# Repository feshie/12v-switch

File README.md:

12v-switch
==========

A simple FET switch with powerpole in/out

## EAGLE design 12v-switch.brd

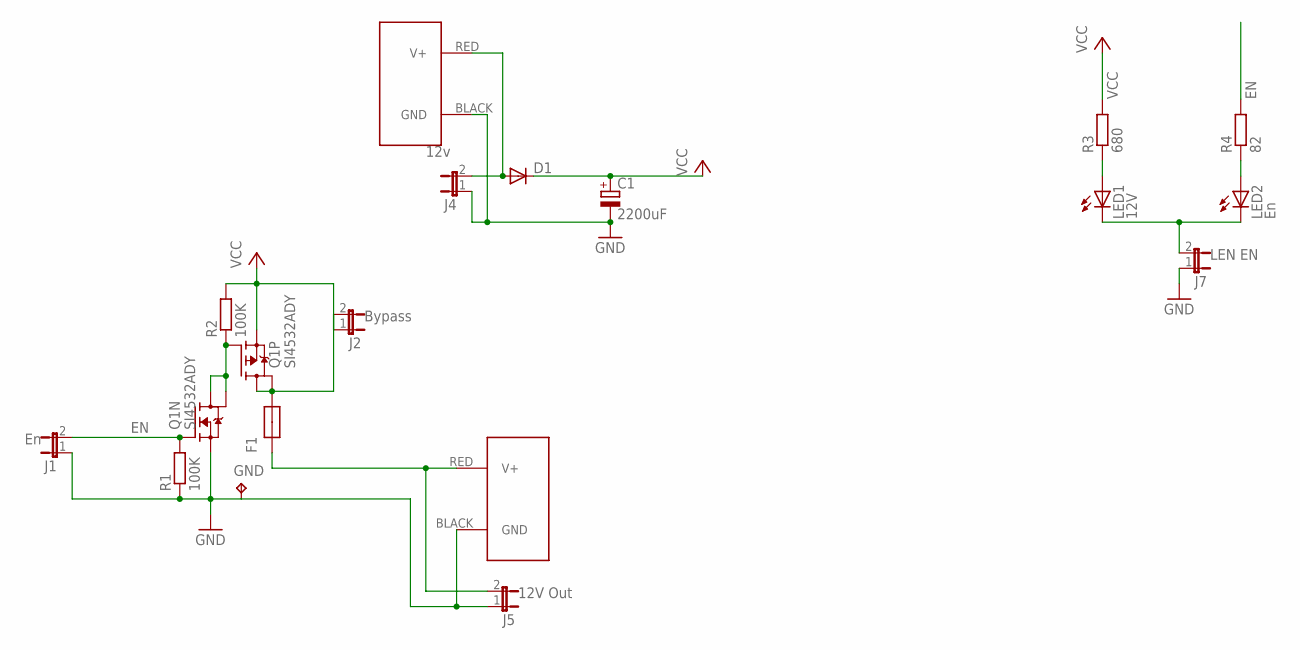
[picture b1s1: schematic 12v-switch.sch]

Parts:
C1: 2200uF; E5-13
D1: DIODE-SMB; SMB
F1: MF-MSMF110; 1812
GND: 5V B; B1,27
J1: En; 2-MOLEX
J2: Bypass; 2-MOLEX
J3, J6: POWERPOLE_POWER25A; POWERPOLE_PAIR_25A
J4: 12v; 2-MOLEX
J5: 12V Out; 2-MOLEX
J7: LEN EN; 2-MOLEX
LED1: 12V; CHIP-LED0805
LED2: En; CHIP-LED0805
Q1: SI4532ADY; SO8
R1, R2: 100K; R0805
R3: 680; R0805
R4: 82; R0805

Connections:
12V-SWITCHED: F1.1, J5.2, J6.RED (V+)
EN: J1.2, Q1.2 (G), R1.2, R4.2
GND: C1.-, GND.TP, J1.1, J3.BLACK (GND), J4.1, J5.1, J6.BLACK (GND), J7.1, Q1.1 (S), R1.1
LEDGND: J7.2, LED1.C, LED2.C
unnamed: D1.A, J3.RED (V+), J4.2
unnamed: LED1.A, R3.1
unnamed: Q1.4 (G), Q1.7 (D), Q1.8 (D), R2.1
unnamed: LED2.A, R4.1
unnamed: F1.2, J2.2, Q1.5 (D), Q1.6 (D)
VCC: C1.+, D1.C, J2.1, Q1.3 (S), R2.2, R3.2

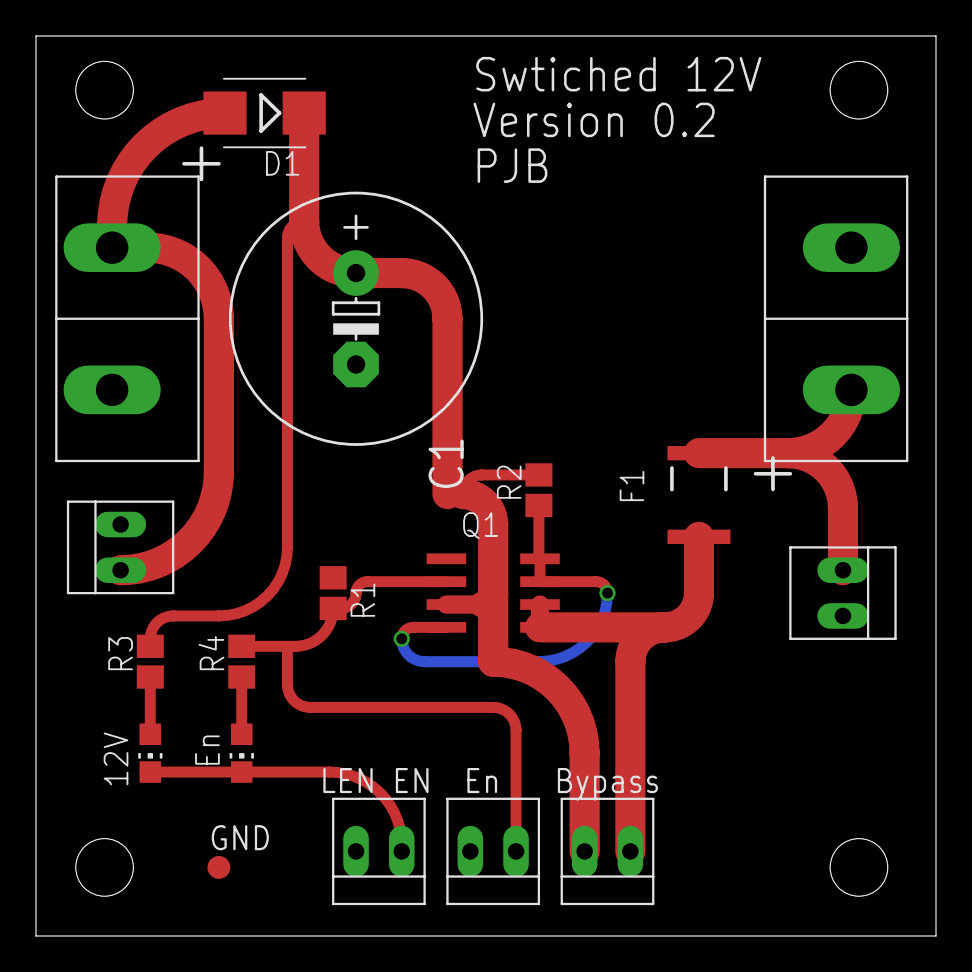
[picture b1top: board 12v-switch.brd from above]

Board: 2 copper layers, 50.0 x 50.0 mm, 18 parts (0 on the bottom side), 10 nets.

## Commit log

2014-05-10 First revision
2014-05-13 output power poles are now compatible with horizontal ones as well as vertical
2014-05-13 added current limit to silk
2014-05-13 minor changes to silk screen
2014-05-14 bump version number for hackvana regeneration
2014-05-27 size of cutter changed to 0.15mm
